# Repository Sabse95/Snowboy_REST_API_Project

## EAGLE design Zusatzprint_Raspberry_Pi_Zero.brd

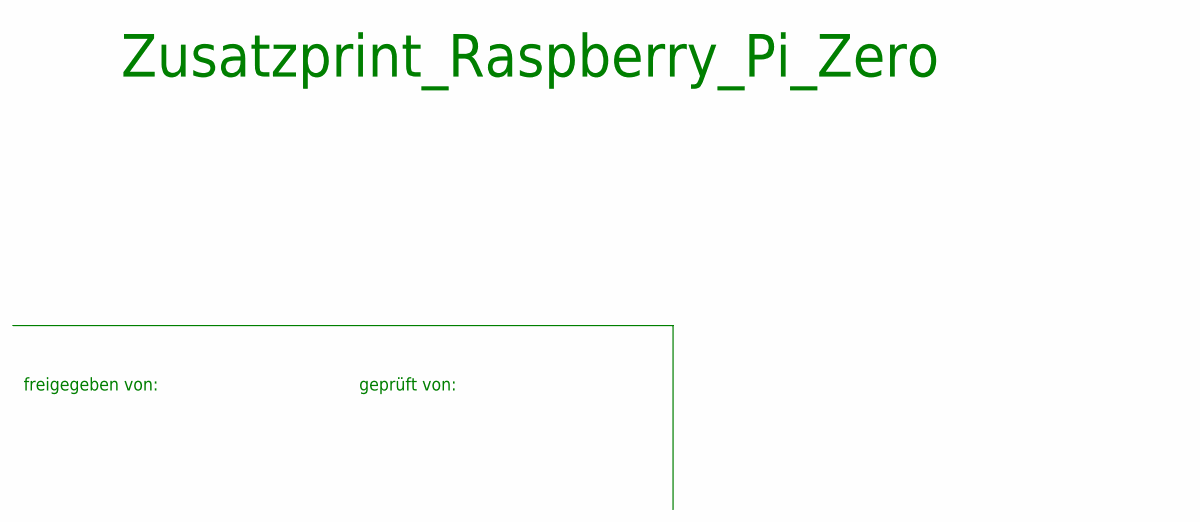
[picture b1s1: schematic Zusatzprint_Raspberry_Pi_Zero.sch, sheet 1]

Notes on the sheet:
Zusatzprint_Raspberry_Pi_Zero
freigegeben von:
geprüft von:

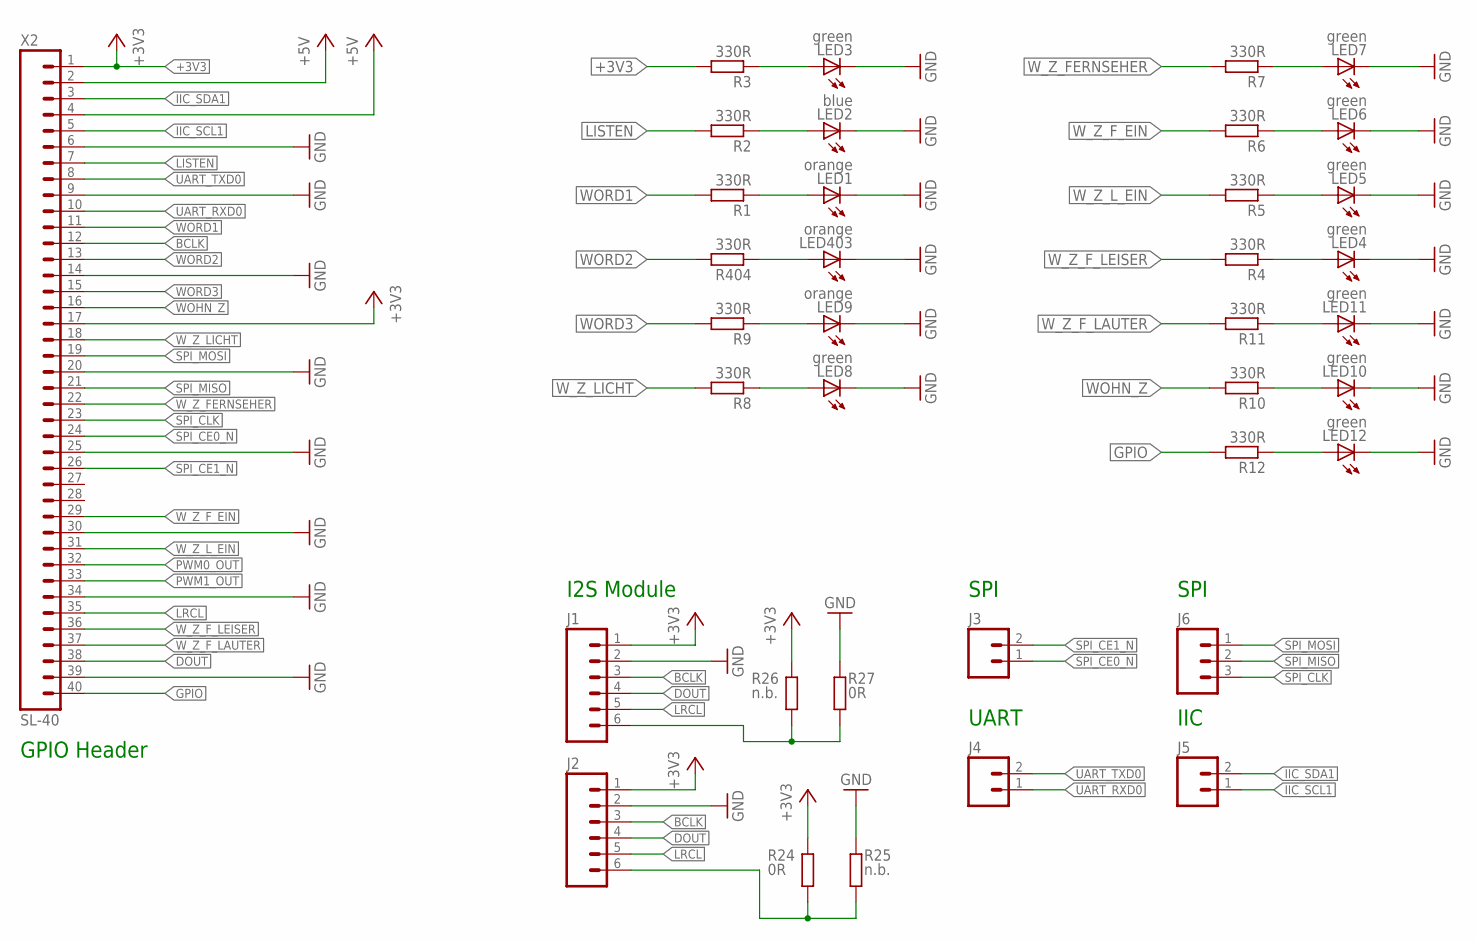
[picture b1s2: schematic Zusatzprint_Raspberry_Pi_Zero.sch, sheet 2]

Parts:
J1, J2: S-LEISTE-06; BL-06
J3, J4, J5: S-LEISTE-02; BL-02
J6: S-LEISTE-03; BL-03
LED1, LED9, LED403: orange; CHIP-LED0805
LED2: blue; CHIP-LED0805
LED3, LED4, LED5, LED6, LED7, LED8, LED10, LED11, LED12: green; CHIP-LED0805
R1, R2, R3, R4, R5, R6, R7, R8, R9, R10, R11, R12, R404: 330R; M0805
R24, R27: 0R; M0805
R25, R26: n.b.; M0805
X2: SL-40; SL_40

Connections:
+3V3: J1.1, J2.1, R3.2, R24.1, R26.1, X2.1, X2.17; also elsewhere on the board
+5V: X2.2, X2.4
BCLK: J1.3, J2.3, X2.12
DOUT: J1.4, J2.4, X2.38
GND: J1.2, J2.2, LED1.C, LED2.C, LED3.C, LED4.C, LED5.C, LED6.C, LED7.C, LED8.C, LED9.C, LED10.C, LED11.C, LED12.C, LED403.C, R25.2, R27.2, X2.6, X2.9, X2.14, X2.20, X2.25, X2.30, X2.34, X2.39; also elsewhere on the board
GPIO: R12.2, X2.40
IIC_SCL1: J5.1, X2.5
IIC_SDA1: J5.2, X2.3
LISTEN: R2.2, X2.7
LRCL: J1.5, J2.5, X2.35
unnamed: LED1.A, R1.1
unnamed: LED2.A, R2.1
unnamed: LED3.A, R3.1
unnamed: LED12.A, R12.1
unnamed: J2.6, R24.2, R25.1
unnamed: J1.6, R26.2, R27.1
unnamed: LED4.A, R4.1
unnamed: LED5.A, R5.1
unnamed: LED6.A, R6.1
unnamed: LED7.A, R7.1
unnamed: LED8.A, R8.1
unnamed: LED9.A, R9.1
unnamed: LED10.A, R10.1
unnamed: LED11.A, R11.1
unnamed: LED403.A, R404.1
PWM0_OUT: X2.32; also elsewhere on the board
PWM1_OUT: X2.33; also elsewhere on the board
SPI_CE0_N: J3.1, X2.24
SPI_CE1_N: J3.2, X2.26
SPI_CLK: J6.3, X2.23
SPI_MISO: J6.2, X2.21
SPI_MOSI: J6.1, X2.19
UART_RXD0: J4.1, X2.10
UART_TXD0: J4.2, X2.8
WOHN_Z: R10.2, X2.16
WORD1: R1.2, X2.11
WORD2: R404.2, X2.13
WORD3: R9.2, X2.15
W_Z_FERNSEHER: R7.2, X2.22
W_Z_F_EIN: R6.2, X2.29
W_Z_F_LAUTER: R11.2, X2.37
W_Z_F_LEISER: R4.2, X2.36
W_Z_LICHT: R8.2, X2.18
W_Z_L_EIN: R5.2, X2.31

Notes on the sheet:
GPIO Header
I2S Module
SPI
UART
IIC

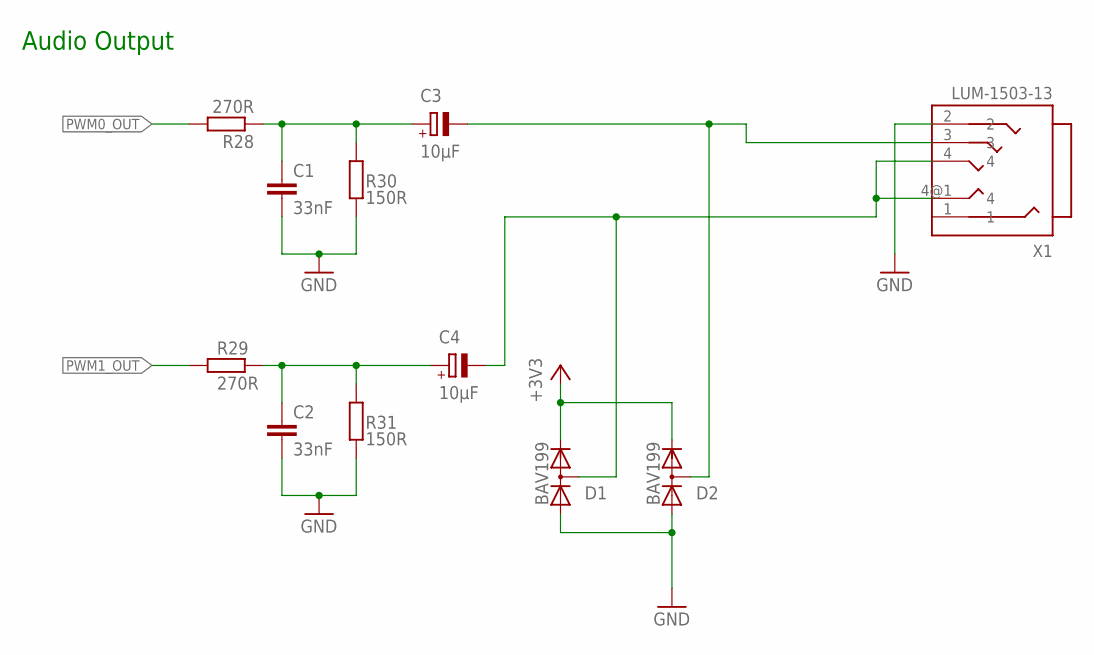
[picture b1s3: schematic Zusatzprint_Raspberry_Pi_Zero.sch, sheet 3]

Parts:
C1, C2: 33nF; C0805
C3, C4: 10µF; E2,5-6
D1, D2: BAV199; SOT23
R28, R29: 270R; M0805
R30, R31: 150R; M0805
X1: LUM-1503-13; 1503-13

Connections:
+3V3: D1.2 (C), D2.2 (C); also elsewhere on the board
GND: C1.2, C2.2, D1.1 (A), D2.1 (A), R30.2, R31.2, X1.2; also elsewhere on the board
unnamed: C1.1, C3.+, R28.1, R30.1
unnamed: C2.1, C4.+, R29.1, R31.1
unnamed: C4.-, D1.3 (AC), X1.4, X1.4@1 (4)
unnamed: C3.-, D2.3 (AC), X1.3
PWM0_OUT: R28.2; also elsewhere on the board
PWM1_OUT: R29.2; also elsewhere on the board

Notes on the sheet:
Audio Output

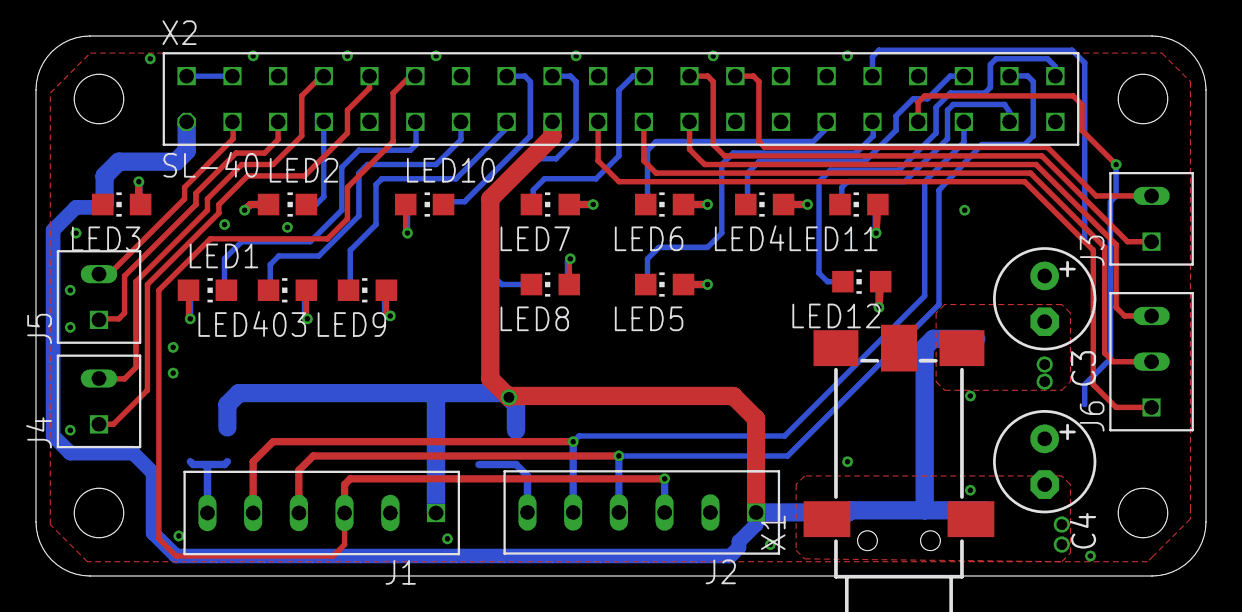
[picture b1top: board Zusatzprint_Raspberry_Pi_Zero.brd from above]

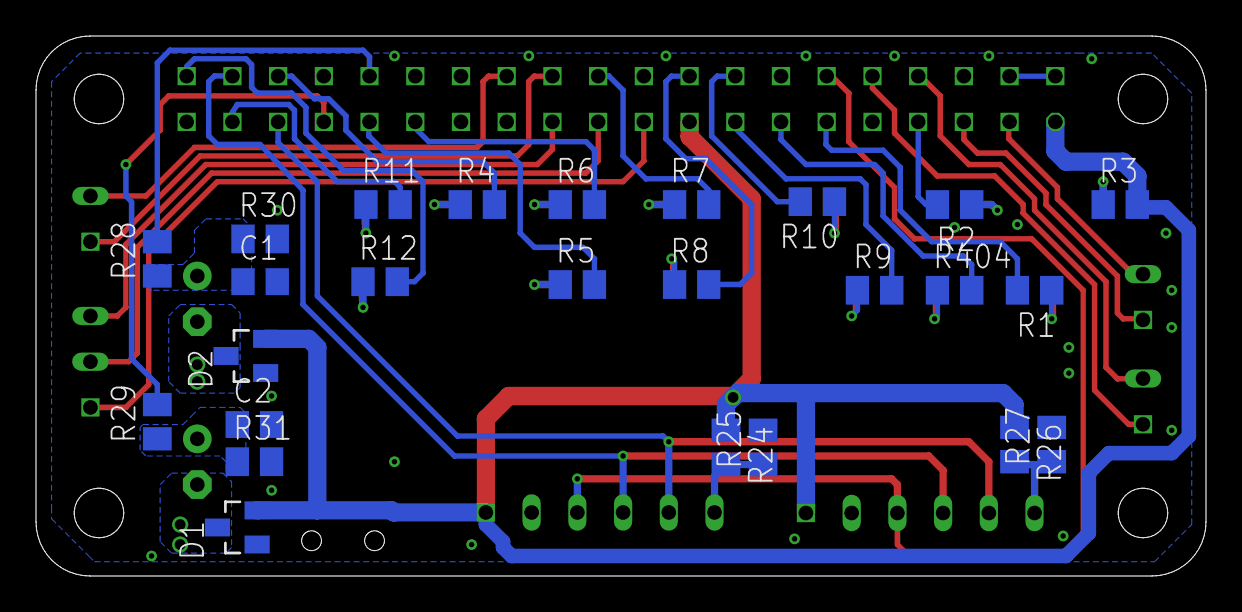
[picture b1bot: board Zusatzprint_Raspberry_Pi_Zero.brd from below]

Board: 4 copper layers, 65.0 x 30.0 mm, 48 parts (25 on the bottom side), 48 nets.

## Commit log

2018-04-25 LED test hinzugefügt
2018-05-08 aenderungen in server applikation
2018-05-08 dynamische config hinzugefügt
2018-05-08 added files
2018-05-11 config anpassungen
2018-05-12 training service und config changed
2018-05-12 Anpassungen configuration und server
2018-05-12 Snowboythreaded demo angepasst
2018-05-12 Anpassungen threade
2018-05-13 server.py detection start und detection terminate hinzugefügt
2018-05-13 Configuration erweitert
2018-05-13 snowboy_recognition und requests und callbacks upgedated
2018-05-14 callbackservice upgedated
2018-05-14 configuration und server upgedated
2018-05-20 Erweiterungsplatine hinzugefügt
    Erweiterungsplatine mit Audioausgang für den Raspberry Pi Zero
2018-05-22 detection LEd geändert
2018-06-09 bugfixing im config.yml
